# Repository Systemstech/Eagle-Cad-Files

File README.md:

Eagle-Cad-Files
===============

These are all my Eagle Cad .brd, sch, and cam generated gerber files

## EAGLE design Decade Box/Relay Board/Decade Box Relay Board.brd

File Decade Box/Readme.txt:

'****************************************************************
'*  Name    : Digi Decade Resistor Box                          *
'*  Author  : Stijn Coenen (Elektronicastynus.be)               *
'*  Notice  : Copyright (c) 2014 Stijn Coenen                   *
'*          : All Rights Reserved                               *
'*  Date    : 19/03/2014                                        *
'*  Version : 1.0                                               *
'*  Notes   :                                                   *
'*          :                                                   *
'****************************************************************

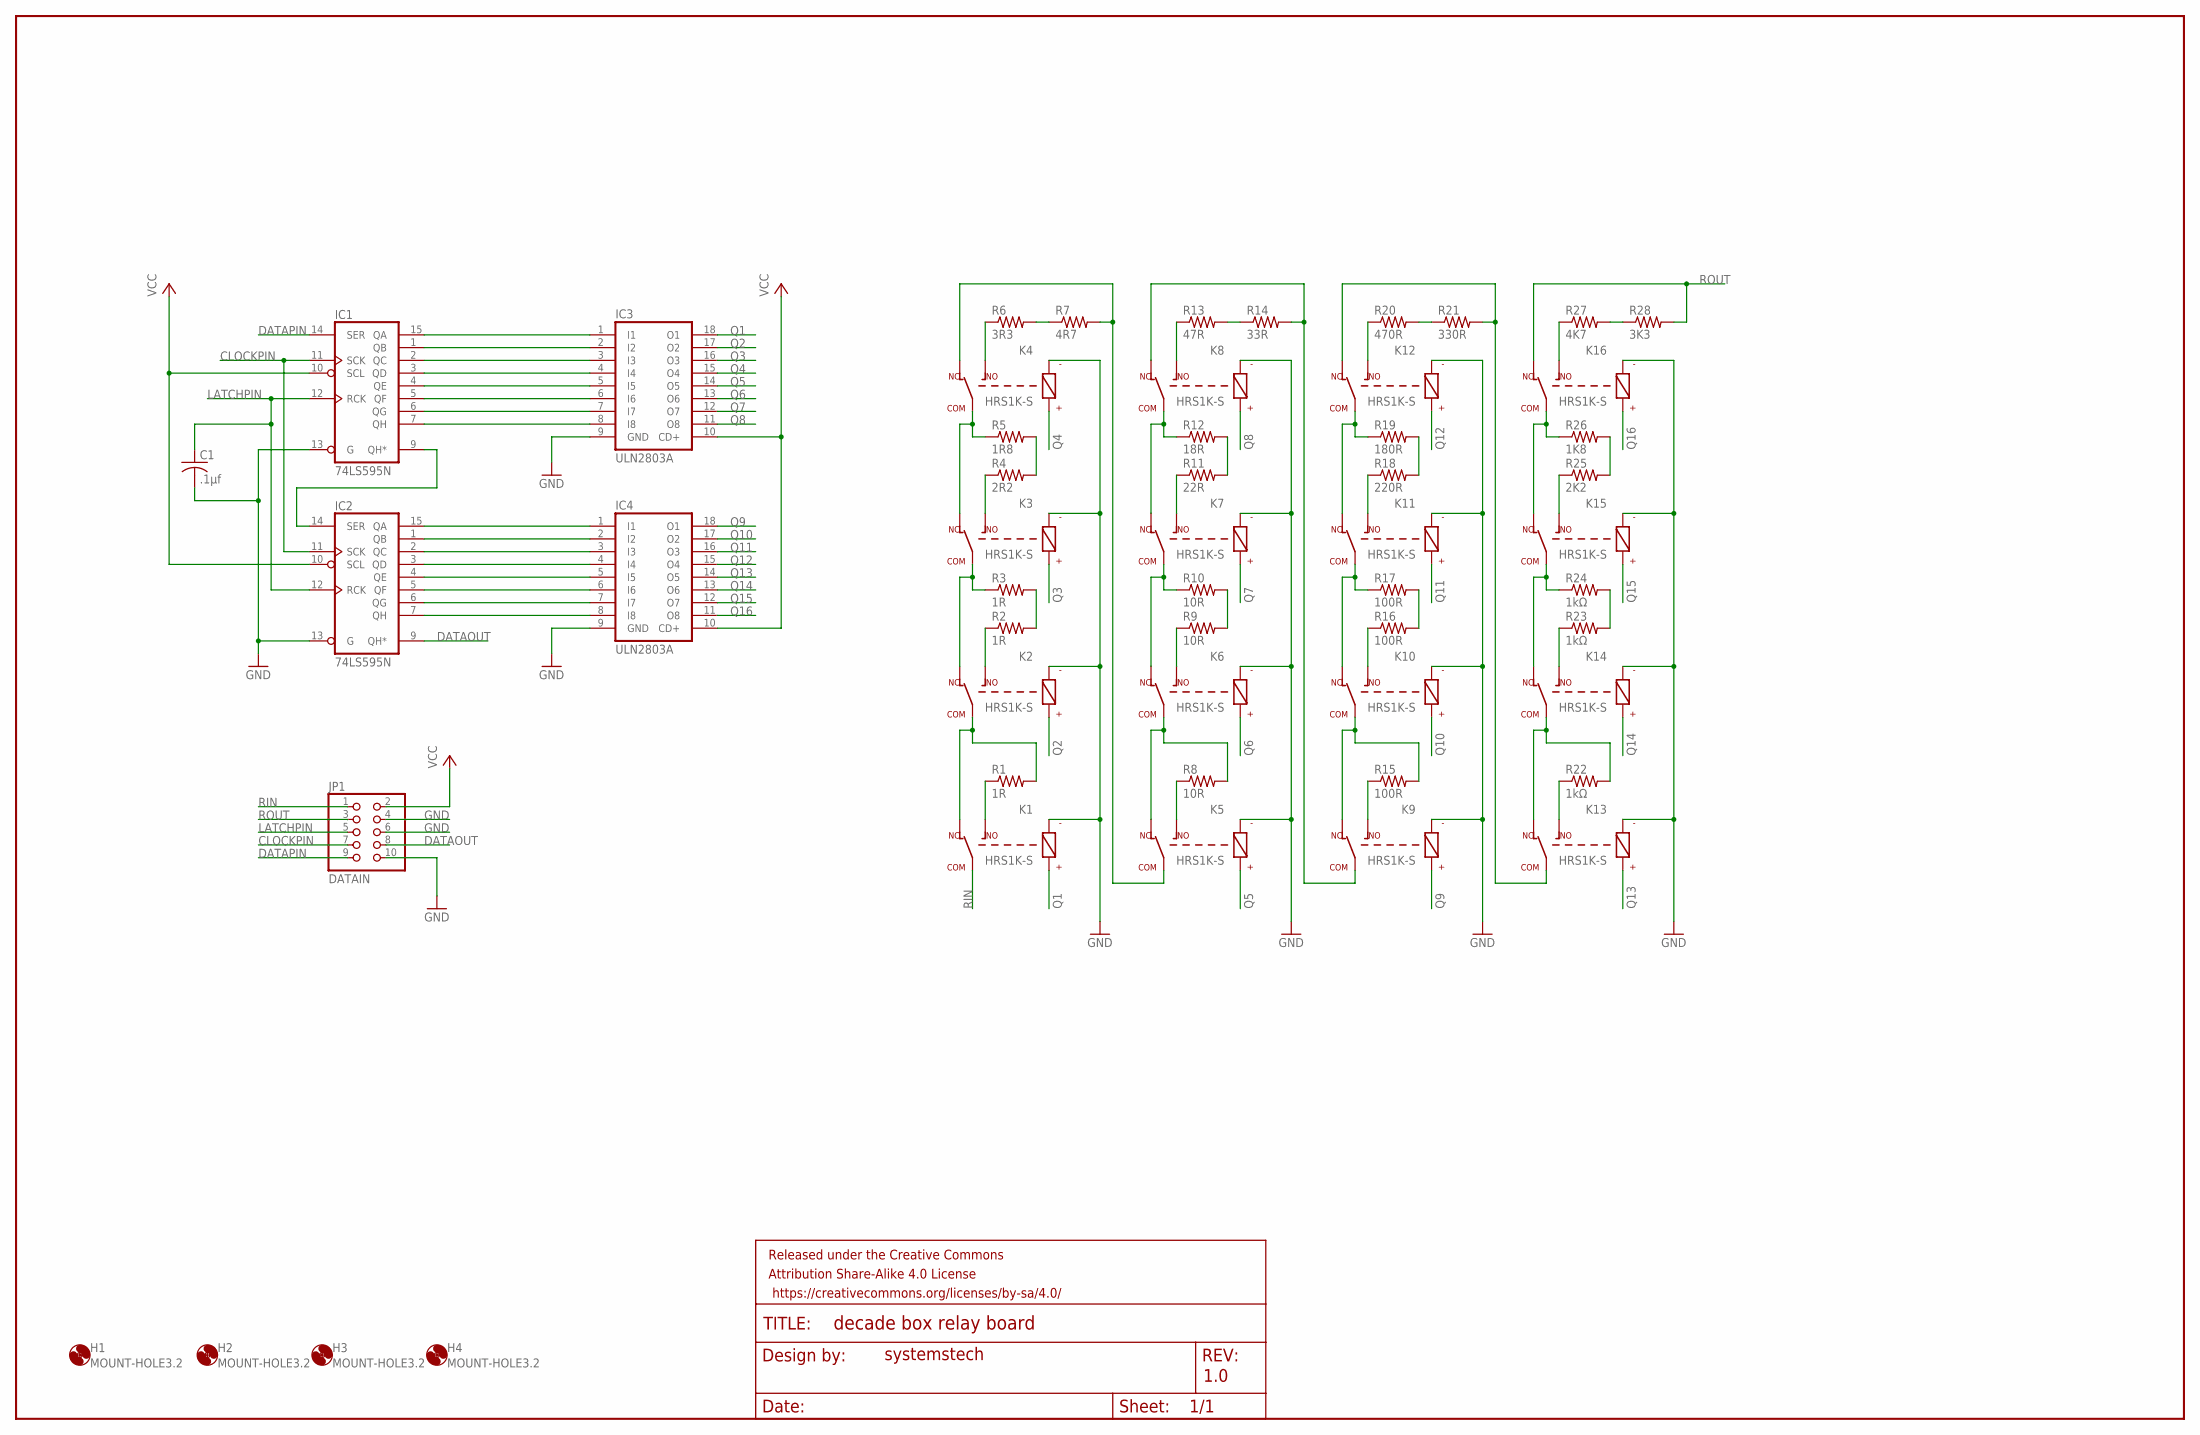
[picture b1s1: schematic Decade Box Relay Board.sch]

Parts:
C1: .1µf; C025-025X050
FRAME1: FRAME-LEDGER; CREATIVE_COMMONS
H1, H2, H3, H4: MOUNT-HOLE3.2; 3,2
IC1, IC2: 74LS595N; DIL16
IC3, IC4: ULN2803A; DIL18
JP1: DATAIN; 2X05
K1, K2, K3, K4, K5, K6, K7, K8, K9, K10, K11, K12, K13, K14, K15, K16: HRS1K-S
R1, R2, R3: 1R; 0411/15
R4: 2R2; 0411/15
R5: 1R8; 0411/15
R6: 3R3; 0411/15
R7: 4R7; 0411/15
R8, R9, R10: 10R; 0411/15
R11: 22R; 0411/15
R12: 18R; 0411/15
R13: 47R; 0411/15
R14: 33R; 0411/15
R15, R16, R17: 100R; 0411/15
R18: 220R; 0411/15
R19: 180R; 0411/15
R20: 470R; 0411/15
R21: 330R; 0411/15
R22, R23, R24: 1kΩ; 0411/15
R25: 2K2; 0411/15
R26: 1K8; 0411/15
R27: 4K7; 0411/15
R28: 3K3; 0411/15

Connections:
CLOCKPIN: IC1.11 (SCK), IC2.11 (SCK), JP1.7
DATAOUT: IC2.9 (QH*), JP1.8
DATAPIN: IC1.14 (SER), JP1.9
GND: C1.2, IC1.8 (GND), IC1.13 (G), IC2.8 (GND), IC2.13 (G), IC3.9 (GND), IC4.9 (GND), JP1.4, JP1.6, JP1.10, K1.P$3 (3), K2.P$3 (3), K3.P$3 (3), K4.P$3 (3), K5.P$3 (3), K6.P$3 (3), K7.P$3 (3), K8.P$3 (3), K9.P$3 (3), K10.P$3 (3), K11.P$3 (3), K12.P$3 (3), K13.P$3 (3), K14.P$3 (3), K15.P$3 (3), K16.P$3 (3)
LATCHPIN: C1.1, IC1.12 (RCK), IC2.12 (RCK), JP1.5
unnamed: K12.P$5 (5), K13.P$1 (1), R21.2
unnamed: K7.P$4 (4), R11.1
unnamed: K15.P$5 (5), K16.P$1 (1), R26.1
unnamed: K1.P$5 (5), K2.P$1 (1), R1.2
unnamed: K10.P$5 (5), K11.P$1 (1), R17.1
unnamed: R9.2, R10.2
unnamed: K8.P$5 (5), K9.P$1 (1), R14.2
unnamed: K4.P$4 (4), R6.1
unnamed: K4.P$5 (5), K5.P$1 (1), R7.2
unnamed: R4.2, R5.2
unnamed: K1.P$4 (4), R1.1
unnamed: IC1.9 (QH*), IC2.14 (SER)
unnamed: K2.P$5 (5), K3.P$1 (1), R3.1
unnamed: K2.P$4 (4), R2.1
unnamed: K11.P$5 (5), K12.P$1 (1), R19.1
unnamed: K3.P$5 (5), K4.P$1 (1), R5.1
unnamed: R2.2, R3.2
unnamed: R11.2, R12.2
unnamed: K5.P$5 (5), K6.P$1 (1), R8.2
unnamed: K3.P$4 (4), R4.1
unnamed: IC1.15 (QA), IC3.1 (I1)
unnamed: K6.P$5 (5), K7.P$1 (1), R10.1
unnamed: R6.2, R7.1
unnamed: K9.P$5 (5), K10.P$1 (1), R15.2
unnamed: K7.P$5 (5), K8.P$1 (1), R12.1
unnamed: K5.P$4 (4), R8.1
unnamed: IC1.1 (QB), IC3.2 (I2)
unnamed: K13.P$5 (5), K14.P$1 (1), R22.2
unnamed: K6.P$4 (4), R9.1
unnamed: K8.P$4 (4), R13.1
unnamed: K14.P$5 (5), K15.P$1 (1), R24.1
unnamed: IC1.2 (QC), IC3.3 (I3)
unnamed: K9.P$4 (4), R15.1
unnamed: IC1.3 (QD), IC3.4 (I4)
unnamed: IC1.4 (QE), IC3.5 (I5)
unnamed: IC1.5 (QF), IC3.6 (I6)
unnamed: IC1.6 (QG), IC3.7 (I7)
unnamed: IC1.7 (QH), IC3.8 (I8)
unnamed: IC2.15 (QA), IC4.1 (I1)
unnamed: IC2.1 (QB), IC4.2 (I2)
unnamed: IC2.2 (QC), IC4.3 (I3)
unnamed: IC2.3 (QD), IC4.4 (I4)
unnamed: IC2.4 (QE), IC4.5 (I5)
unnamed: IC2.5 (QF), IC4.6 (I6)
unnamed: IC2.6 (QG), IC4.7 (I7)
unnamed: IC2.7 (QH), IC4.8 (I8)
unnamed: R13.2, R14.1
unnamed: K10.P$4 (4), R16.1
unnamed: R16.2, R17.2
unnamed: K11.P$4 (4), R18.1
unnamed: R18.2, R19.2
unnamed: K12.P$4 (4), R20.1
unnamed: R20.2, R21.1
unnamed: K13.P$4 (4), R22.1
unnamed: K14.P$4 (4), R23.1
unnamed: R23.2, R24.2
unnamed: K15.P$4 (4), R25.1
unnamed: R25.2, R26.2
unnamed: K16.P$4 (4), R27.1
unnamed: R27.2, R28.1
Q1: IC3.18 (O1), K1.P$2 (2)
Q2: IC3.17 (O2), K2.P$2 (2)
Q3: IC3.16 (O3), K3.P$2 (2)
Q4: IC3.15 (O4), K4.P$2 (2)
Q5: IC3.14 (O5), K5.P$2 (2)
Q6: IC3.13 (O6), K6.P$2 (2)
Q7: IC3.12 (O7), K7.P$2 (2)
Q8: IC3.11 (O8), K8.P$2 (2)
Q9: IC4.18 (O1), K9.P$2 (2)
Q10: IC4.17 (O2), K10.P$2 (2)
Q11: IC4.16 (O3), K11.P$2 (2)
Q12: IC4.15 (O4), K12.P$2 (2)
Q13: IC4.14 (O5), K13.P$2 (2)
Q14: IC4.13 (O6), K14.P$2 (2)
Q15: IC4.12 (O7), K15.P$2 (2)
Q16: IC4.11 (O8), K16.P$2 (2)
RIN: JP1.1, K1.P$1 (1)
ROUT: JP1.3, K16.P$5 (5), R28.2
VCC: IC1.10 (SCL), IC1.16 (VCC), IC2.10 (SCL), IC2.16 (VCC), IC3.10 (CD+), IC4.10 (CD+), JP1.2

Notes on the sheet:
systemstech
1.0

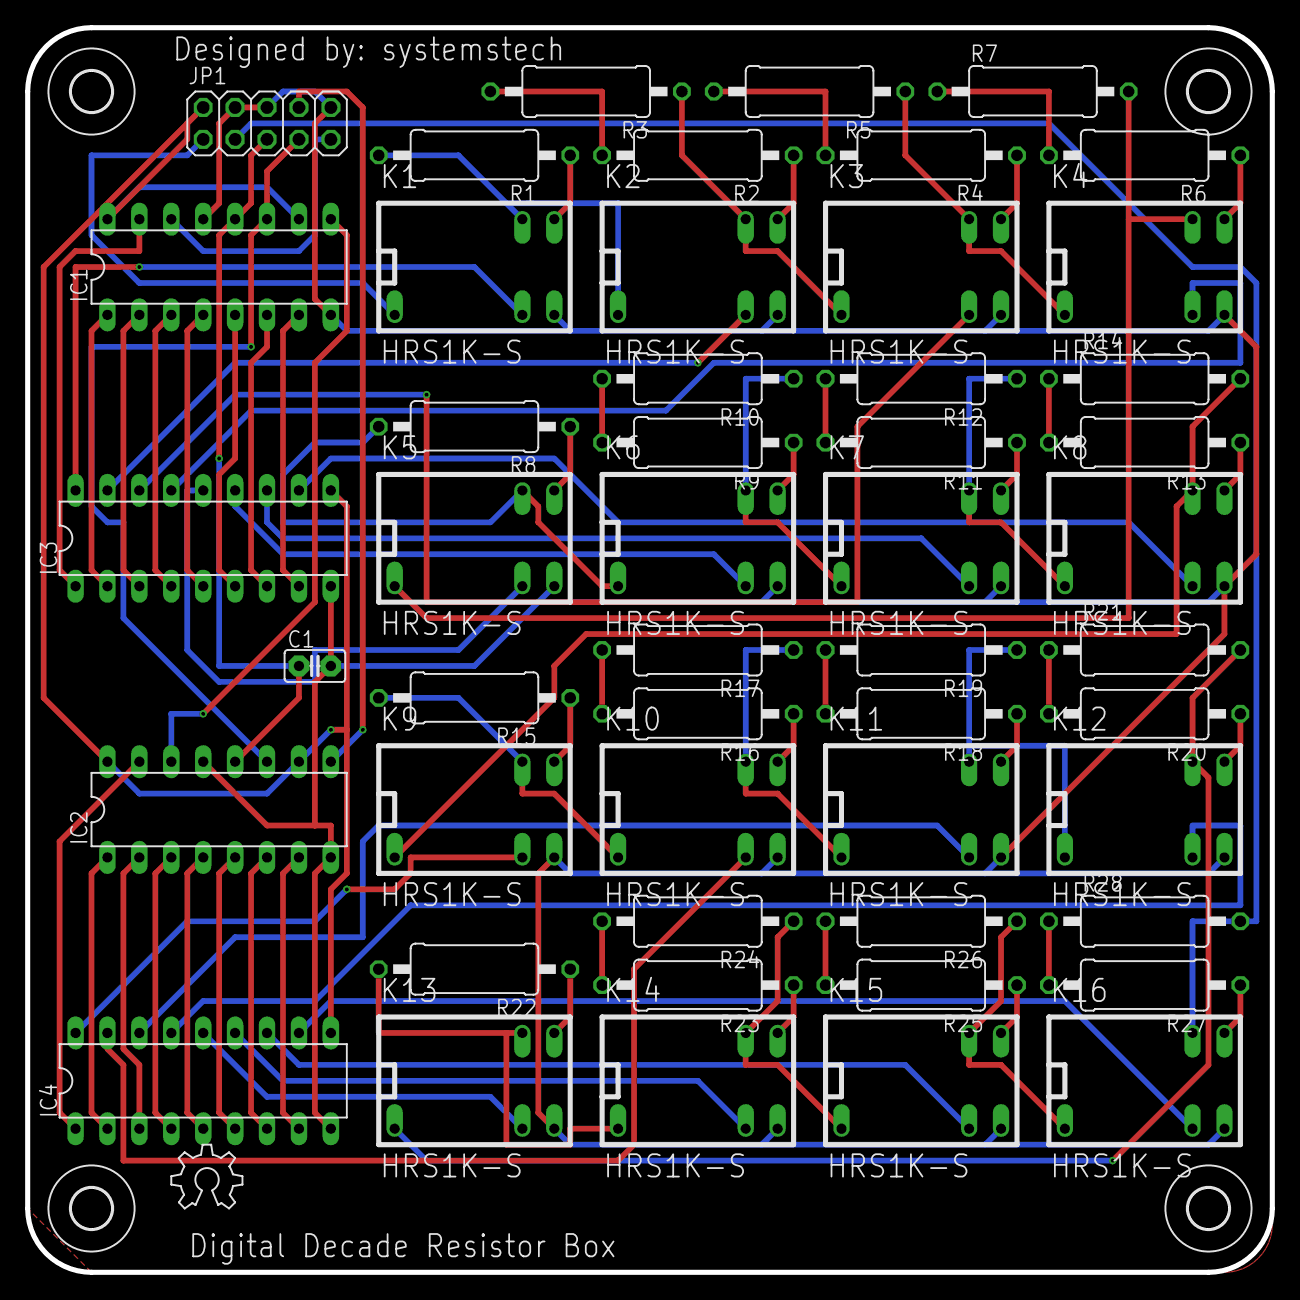
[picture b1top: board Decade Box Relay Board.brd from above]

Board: 2 copper layers, 99.1 x 99.1 mm, 56 parts (0 on the bottom side), 84 nets.

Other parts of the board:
U$10: OSHW_6X200_NOTEXT

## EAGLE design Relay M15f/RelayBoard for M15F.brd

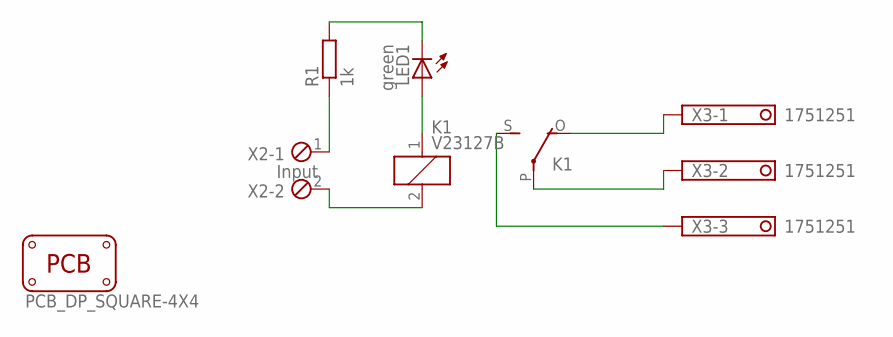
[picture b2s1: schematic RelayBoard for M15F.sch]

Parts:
K1: V23127B
LED1: green; LED-805
PCB1: PCB_DP_SQUARE-4X4; DP4040_V1
R1: 1k; R805
X2: Input; 2POL254
X3: 1751251

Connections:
unnamed: R1.1, X2.1
unnamed: LED1.C, R1.2
unnamed: K1.1, LED1.A
unnamed: K1.2, X2.2
unnamed: K1.P, X3.2
unnamed: K1.O, X3.1
unnamed: K1.S, X3.3

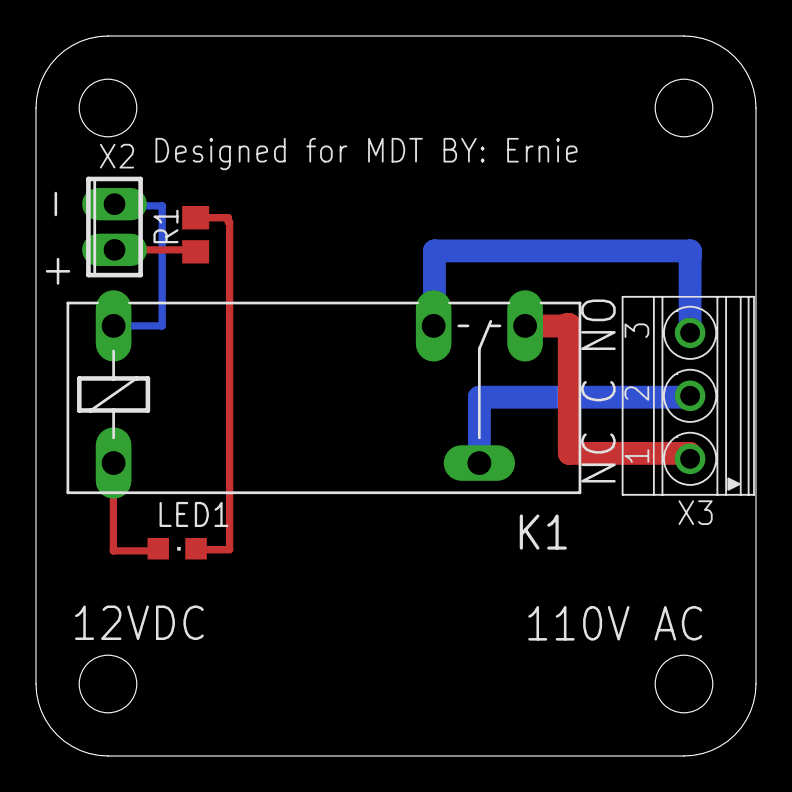
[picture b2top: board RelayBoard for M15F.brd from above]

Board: 2 copper layers, 40.0 x 40.0 mm, 6 parts (0 on the bottom side), 7 nets.

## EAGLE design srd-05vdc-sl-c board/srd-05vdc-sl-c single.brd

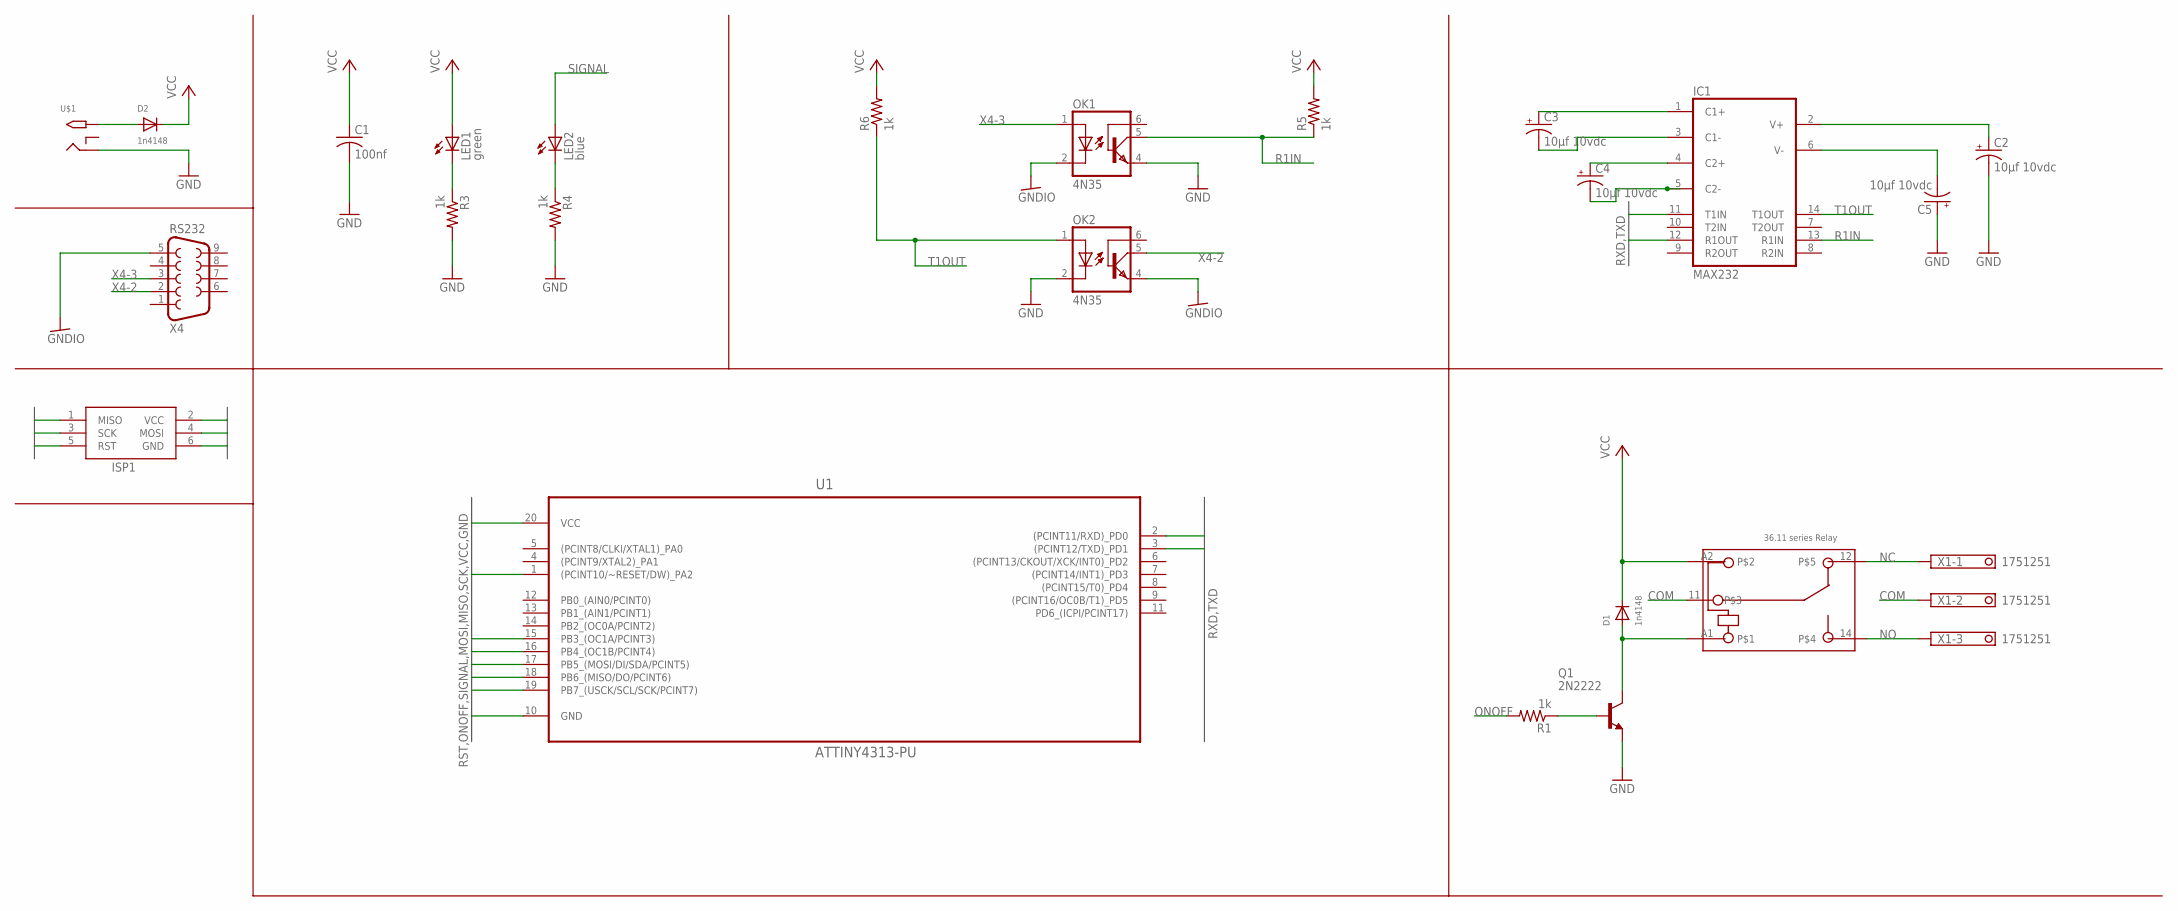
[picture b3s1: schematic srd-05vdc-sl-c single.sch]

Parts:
C1: 100nf; C025-025X050
C2, C3, C4, C5: 10µf 10vdc; E2,5-6
D1, D2: 1n4148; DO-1N4148
IC1: MAX232; DIL16
ISP1: AVRISP-6; AVRISP
LED1: green; LED3MM
LED2: blue; LED3MM
OK1, OK2: 4N35; DIL06
Q1: 2N2222; TO92-EBC-OVAL
R1, R3, R4, R5, R6: 1k; 0204/7
SRD-05VDC-SL-C: 36.11
U1: ATTINY4313-PU; DIP254P762X533-20
U$1: 2.1MMJACKTHM; PJ-102A
X1: 1751251
X4: RS232; F09H

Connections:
COM: SRD-05VDC-SL-C.11, X1.2
GND: C1.2, C2.-, C5.+, IC1.15 (GND), ISP1.6 (GND), OK1.4 (EMI), OK2.2 (C), Q1.E, R3.2, R4.2, U1.10 (GND), U$1.RING
GNDIO: OK1.2 (C), OK2.4 (EMI), X4.5
MISO: ISP1.1 (MISO), U1.18 (PB6_(MISO/DO/PCINT6))
MOSI: ISP1.4 (MOSI), U1.17 (PB5_(MOSI/DI/SDA/PCINT5))
unnamed: C5.-, IC1.6 (V-)
unnamed: D2.A, U$1.TIP
unnamed: LED1.K (C), R3.1
unnamed: LED2.K (C), R4.1
unnamed: D1.A, Q1.C, SRD-05VDC-SL-C.A1
unnamed: Q1.B, R1.1
unnamed: C3.+, IC1.1 (C1+)
unnamed: C3.-, IC1.3 (C1-)
unnamed: C4.+, IC1.4 (C2+)
unnamed: C4.-, IC1.5 (C2-)
unnamed: C2.+, IC1.2 (V+)
NC: SRD-05VDC-SL-C.12, X1.1
NO: SRD-05VDC-SL-C.14, X1.3
ONOFF: R1.2, U1.15 (PB3_(OC1A/PCINT3))
R1IN: IC1.13 (R1IN), OK1.5 (COL), R5.1
RST: ISP1.5 (RST), U1.1 ((PCINT10/~RESET/DW)_PA2)
RXD: IC1.12 (R1OUT), U1.2 ((PCINT11/RXD)_PD0)
SCK: ISP1.3 (SCK), U1.19 (PB7_(USCK/SCL/SCK/PCINT7))
SIGNAL: LED2.A, U1.16 (PB4_(OC1B/PCINT4))
T1OUT: IC1.14 (T1OUT), OK2.1 (A), R6.1
TXD: IC1.11 (T1IN), U1.3 ((PCINT12/TXD)_PD1)
VCC: C1.1, D1.C, D2.C, IC1.16 (VCC), ISP1.2 (VCC), LED1.A, R5.2, R6.2, SRD-05VDC-SL-C.A2, U1.20 (VCC)
X4-2: OK2.5 (COL), X4.2
X4-3: OK1.1 (A), X4.3

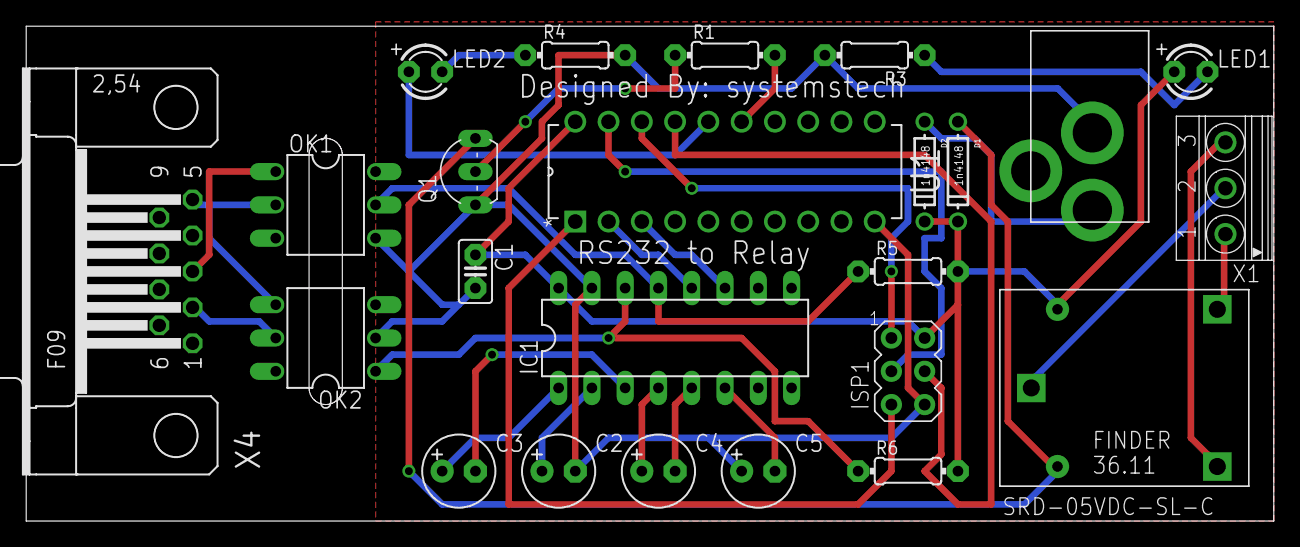
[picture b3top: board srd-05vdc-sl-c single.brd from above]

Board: 2 copper layers, 95.2 x 37.8 mm, 25 parts (0 on the bottom side), 29 nets.

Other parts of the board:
U$2: OSHWLOGO_TOL_0.2

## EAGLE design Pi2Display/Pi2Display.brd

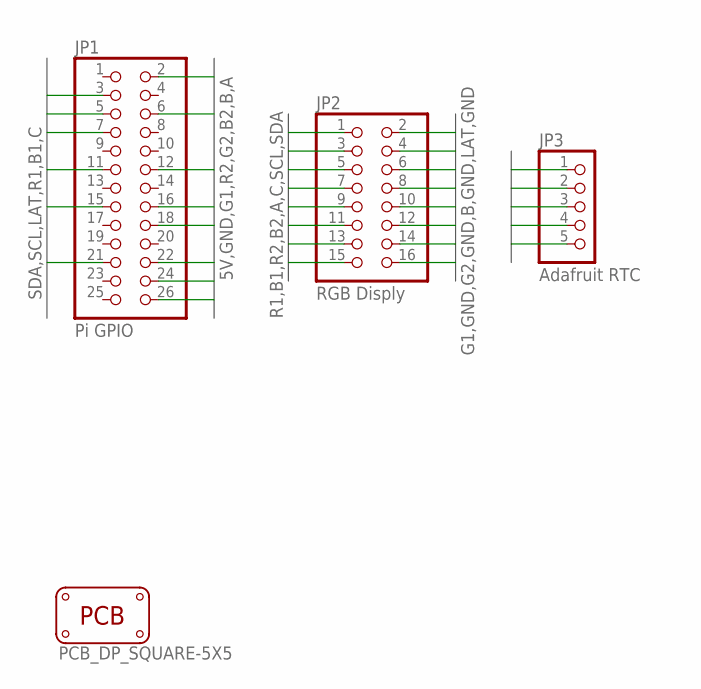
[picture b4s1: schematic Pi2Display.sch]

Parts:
JP1: Pi GPIO; 2X13
JP2: RGB Disply; 2X08
JP3: Adafruit RTC; 1X05
PCB1: PCB_DP_SQUARE-5X5; DP5050_V1

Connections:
5V: JP1.2, JP3.2
A: JP1.26, JP2.9
B: JP1.24, JP2.10
B1: JP1.15, JP2.3
B2: JP1.22, JP2.7
C: JP1.21, JP2.11
G1: JP1.12, JP2.2
G2: JP1.18, JP2.6
GND: JP1.6, JP2.4, JP2.8, JP2.12, JP2.16, JP3.1
LAT: JP1.7, JP2.14
R1: JP1.11, JP2.1
R2: JP1.16, JP2.5
SCL: JP1.5, JP2.13, JP3.4
SDA: JP1.3, JP2.15, JP3.3
SQW: JP3.5

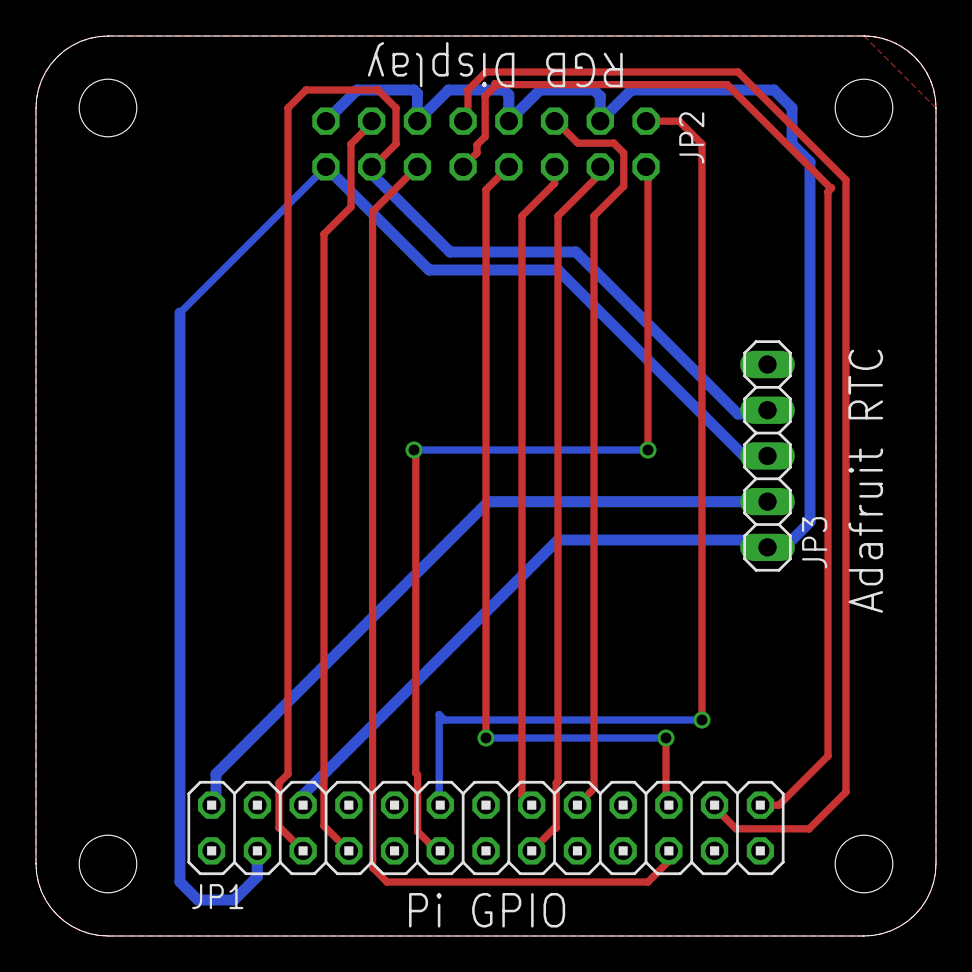
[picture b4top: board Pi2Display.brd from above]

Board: 2 copper layers, 50.0 x 50.0 mm, 4 parts (1 on the bottom side), 14 nets.

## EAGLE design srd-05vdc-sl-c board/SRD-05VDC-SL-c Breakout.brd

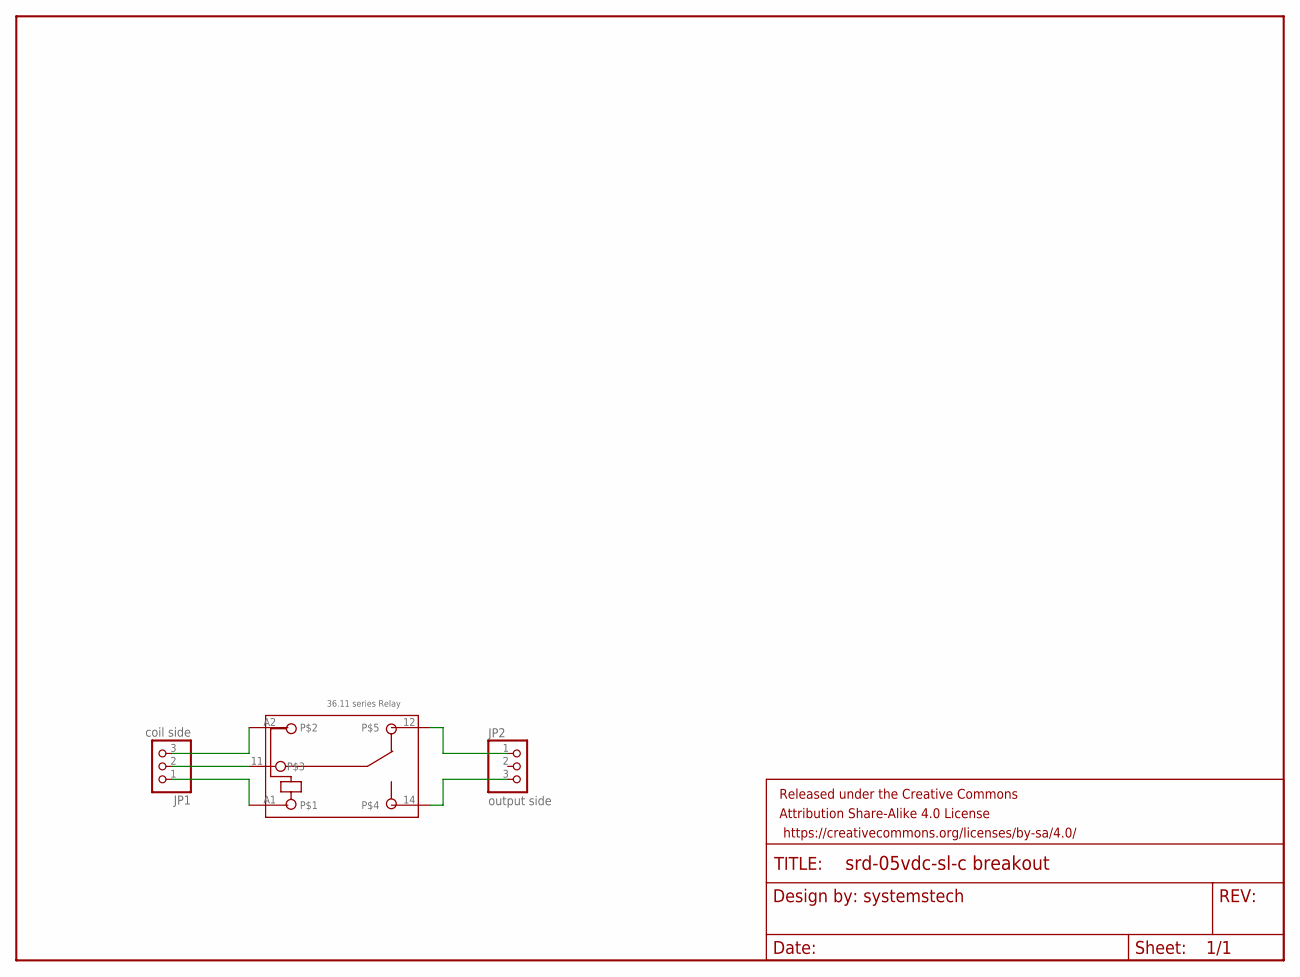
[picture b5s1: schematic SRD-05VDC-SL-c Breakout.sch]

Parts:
FRAME1: FRAME-LETTER; CREATIVE_COMMONS
JP1: coil side; 1X03
JP2: output side; 1X03
K1: 36.11

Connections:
unnamed: JP1.3, K1.A2
unnamed: JP1.2, K1.11
unnamed: JP1.1, K1.A1
unnamed: JP2.1, K1.12
unnamed: JP2.3, K1.14

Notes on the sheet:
systemstech

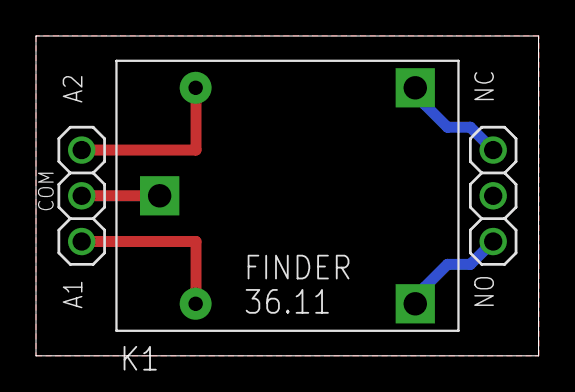
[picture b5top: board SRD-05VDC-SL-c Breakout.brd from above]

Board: 2 copper layers, 27.9 x 17.8 mm, 6 parts (1 on the bottom side), 5 nets.

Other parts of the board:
U$1: CREATIVE_COMMONS
U$2: OSHW-LOGO-S

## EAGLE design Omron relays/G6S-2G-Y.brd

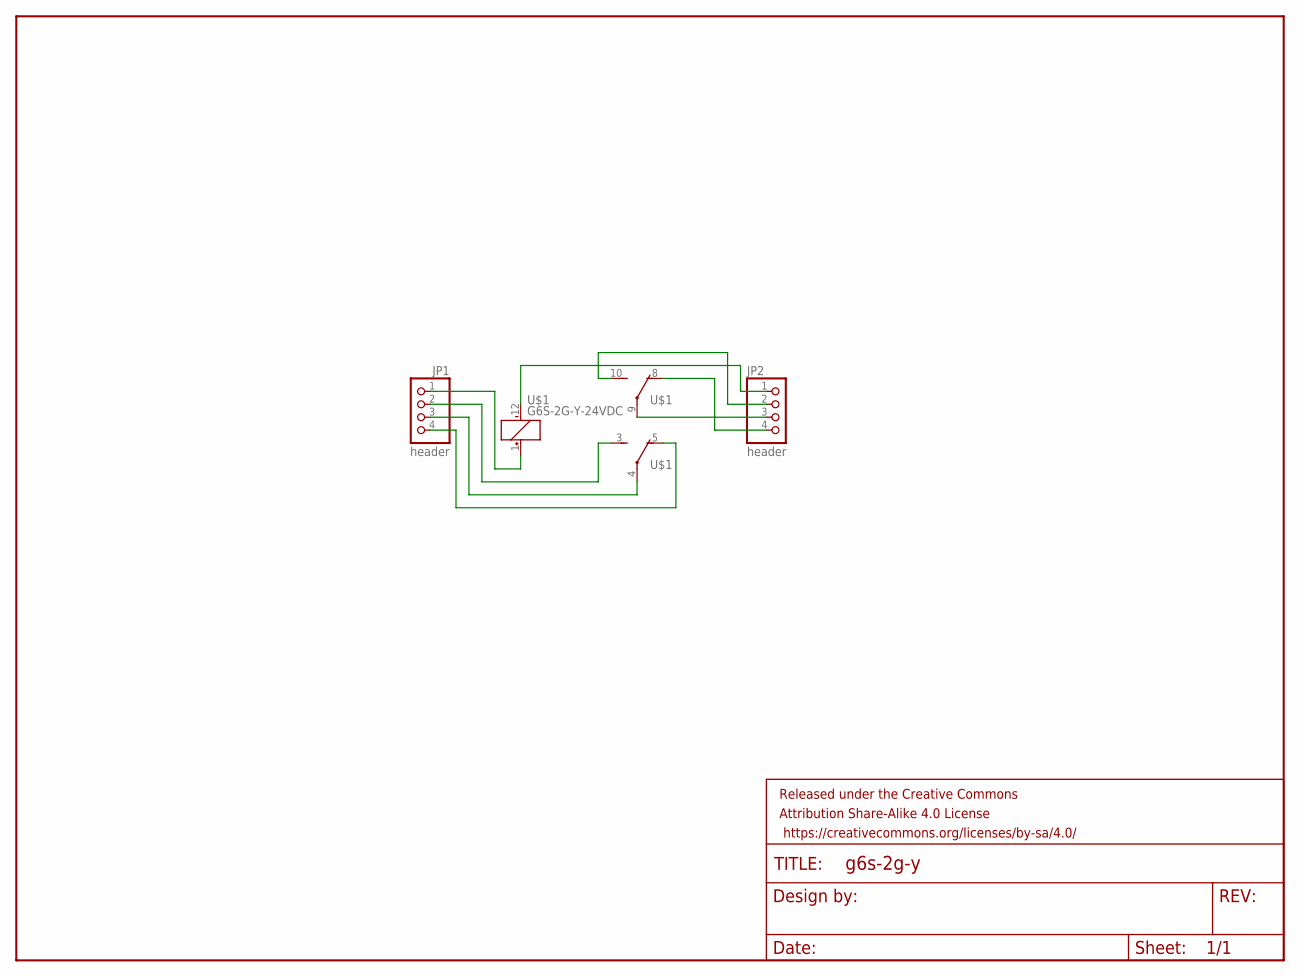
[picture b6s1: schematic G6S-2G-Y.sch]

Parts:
FRAME1: FRAME-LETTER; CREATIVE_COMMONS
JP1, JP2: header; 1X04
U$1: G6S-2G-Y-24VDC

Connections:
unnamed: JP1.1, U$1.1 (+)
unnamed: JP1.2, U$1.3 (NO)
unnamed: JP1.3, U$1.4 (COM)
unnamed: JP1.4, U$1.5 (NC)
unnamed: JP2.1, U$1.12 (-)
unnamed: JP2.2, U$1.10 (NO)
unnamed: JP2.3, U$1.9 (COM)
unnamed: JP2.4, U$1.8 (NC)

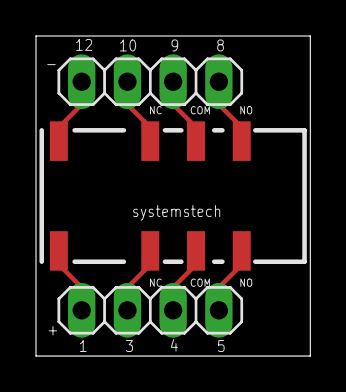
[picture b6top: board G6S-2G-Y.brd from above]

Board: 2 copper layers, 15.2 x 17.8 mm, 4 parts (0 on the bottom side), 8 nets.

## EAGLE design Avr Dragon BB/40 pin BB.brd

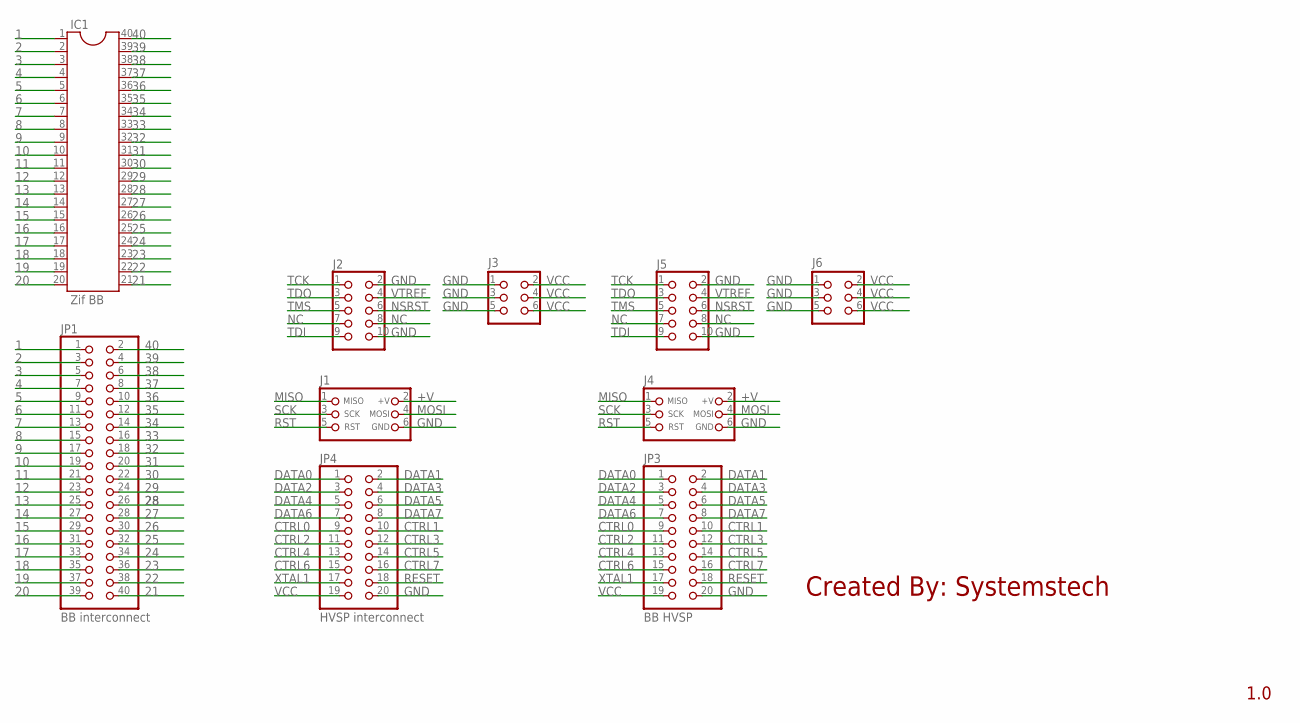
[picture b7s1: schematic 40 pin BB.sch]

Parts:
IC1: Zif BB; DIL40
J1, J4: CON_HEADER_PRG_AVR_ICSP; HEADER_PRG_2X03
J2, J5: CON_HEADER_2X05-PTH; M2X5
J3, J6: CON_HEADER_2X03-PTH; M2X3
JP1: BB interconnect; 2X20
JP3: BB HVSP; 2X10
JP4: HVSP interconnect; 2X10

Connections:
1: IC1.1, JP1.1
2: IC1.2, JP1.3
3: IC1.3, JP1.5
4: IC1.4, JP1.7
5: IC1.5, JP1.9
6: IC1.6, JP1.11
7: IC1.7, JP1.13
8: IC1.8, JP1.15
9: IC1.9, JP1.17
10: IC1.10, JP1.19
11: IC1.11, JP1.21
12: IC1.12, JP1.23
13: IC1.13, JP1.25
14: IC1.14, JP1.27
15: IC1.15, JP1.29
16: IC1.16, JP1.31
17: IC1.17, JP1.33
18: IC1.18, JP1.35
19: IC1.19, JP1.37
20: IC1.20, JP1.39
21: IC1.21, JP1.40
22: IC1.22, JP1.38
23: IC1.23, JP1.36
24: IC1.24, JP1.34
25: IC1.25, JP1.32
26: IC1.26, JP1.30
27: IC1.27, JP1.28
28: IC1.28, JP1.26
29: IC1.29, JP1.24
30: IC1.30, JP1.22
31: IC1.31, JP1.20
32: IC1.32, JP1.18
33: IC1.33, JP1.16
34: IC1.34, JP1.14
35: IC1.35, JP1.12
36: IC1.36, JP1.10
37: IC1.37, JP1.8
38: IC1.38, JP1.6
39: IC1.39, JP1.4
40: IC1.40, JP1.2
+V: J1.2 (+V), J4.2 (+V)
CTRL0: JP3.9, JP4.9
CTRL1: JP3.10, JP4.10
CTRL2: JP3.11, JP4.11
CTRL3: JP3.12, JP4.12
CTRL4: JP3.13, JP4.13
CTRL5: JP3.14, JP4.14
CTRL6: JP3.15, JP4.15
CTRL7: JP3.16, JP4.16
DATA0: JP3.1, JP4.1
DATA1: JP3.2, JP4.2
DATA2: JP3.3, JP4.3
DATA3: JP3.4, JP4.4
DATA4: JP3.5, JP4.5
DATA5: JP3.6, JP4.6
DATA6: JP3.7, JP4.7
DATA7: JP3.8, JP4.8
GND: J1.6 (GND), J2.2, J2.10, J3.1, J3.3, J3.5, J4.6 (GND), J5.2, J5.10, J6.1, J6.3, J6.5, JP3.20, JP4.20
MISO: J1.1 (MISO), J4.1 (MISO)
MOSI: J1.4 (MOSI), J4.4 (MOSI)
NC: J2.7, J2.8, J5.7, J5.8
NSRST: J2.6, J5.6
RESET: JP3.18, JP4.18
RST: J1.5 (RST), J4.5 (RST)
SCK: J1.3 (SCK), J4.3 (SCK)
TCK: J2.1, J5.1
TDI: J2.9, J5.9
TDO: J2.3, J5.3
TMS: J2.5, J5.5
VCC: J3.2, J3.4, J3.6, J6.2, J6.4, J6.6, JP3.19, JP4.19
VTREF: J2.4, J5.4
XTAL1: JP3.17, JP4.17

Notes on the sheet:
Created By: Systemstech
1.0

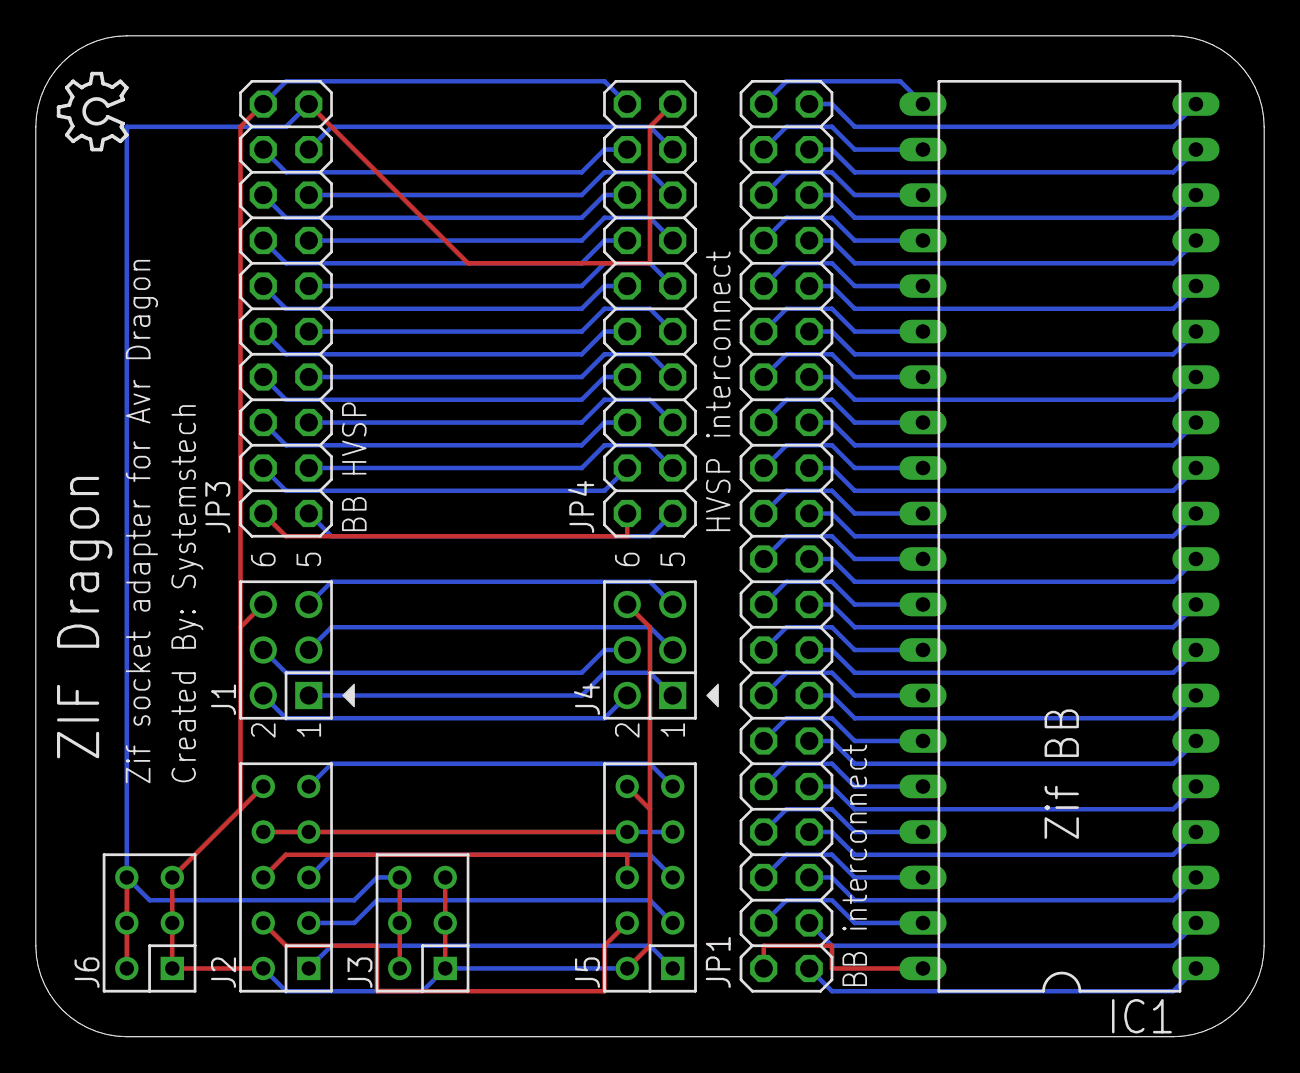
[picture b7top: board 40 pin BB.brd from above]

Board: 5 copper layers, 68.6 x 55.9 mm, 11 parts (0 on the bottom side), 72 nets.

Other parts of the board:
U$1: OSHW_8X150_NOTEXT

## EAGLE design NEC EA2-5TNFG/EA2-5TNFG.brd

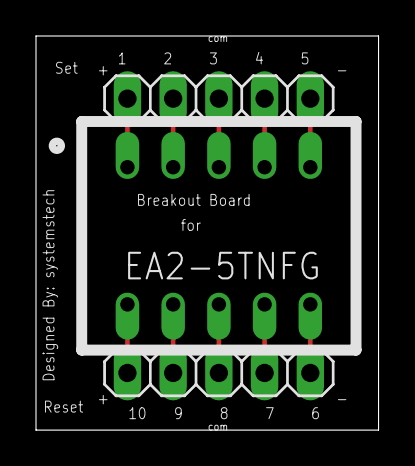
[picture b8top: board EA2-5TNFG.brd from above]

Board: 2 copper layers, 19.0 x 21.9 mm, 5 parts (1 on the bottom side), 10 nets.

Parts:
FRAME1: FRAME-LETTER; CREATIVE_COMMONS
JP3, JP4: 1X05
U$1: EA2-5TNFG; EA2-SERIES-RELAY
U$2: OSHW-LOGO-M

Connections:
unnamed: JP4.5, U$1.P$10
unnamed: JP4.4, U$1.P$9
unnamed: JP4.3, U$1.P$8
unnamed: JP4.2, U$1.P$7
unnamed: JP4.1, U$1.P$6
unnamed: JP3.5, U$1.P$5
unnamed: JP3.4, U$1.P$4
unnamed: JP3.3, U$1.P$3
unnamed: JP3.2, U$1.P$2
unnamed: JP3.1, U$1.P$1

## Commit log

2014-09-21 AVR Dragon Adapter
    Breakout board for the AVR Dragon 40pin module.
2014-09-21 BreakoutBoards
    Added more breakout board directories
2014-09-21 G6S-2G-Y
    Omron G6S-2G-Y relay breakout board.
2014-09-21 EA2-5TNFG
    NEC EA2-5TNFG relay breakout board
2014-09-22 M15F 12vdc relay
    project for work, intrusion alarm relay.
2014-09-22 Gerbers
    Gerber files for fab house.
2014-09-22 Eagle Cad
    My Eagle Cad brd, sch files
2014-10-04 Digital Decade Resistor Box

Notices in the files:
parts and their libraries:
SparkFun-Aesthetics: Licensing: Creative Commons ShareAlike 4.0 International - https://creativecommons.org/licenses/by-sa/4.0
SparkFun-Aesthetics: Released under the Creative Commons Attribution Share-Alike 4.0 License
SparkFun-Aesthetics: https://creativecommons.org/licenses/by-sa/4.0
